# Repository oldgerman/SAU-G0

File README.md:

## SAU-G0

> 某存在感很弱的屑温湿度计（），美其名曰 Sensor Acquisition Unit（传感器采集单元）

- [1. 简介](#1-简介)
- [2. 续航](#2-续航)
  - [最低电流](#最低电流)
  - [最高电流](#最高电流)
  - [理论续航时间](#理论续航时间)
- [3. PCB](#3-pcb)
  - [SAU-G0（主控板）](#sau-g0主控板)
  - [SAU-G0-EX_AHT-GL（拓展版-AHT温湿度计-普通级）](#sau-g0-ex_aht-gl拓展版-aht温湿度计-普通级)
  - [SAU-G0-EX_AHT-PL（拓展版-AHT温湿度计-精准级）](#sau-g0-ex_aht-pl拓展版-aht温湿度计-精准级)
  - [SAU-G0-EX_microSD（拓展版-microSD）](#sau-g0-ex_microsd拓展版-microsd)
- [4. 焊接](#4-焊接)
- [5. BOM](#5-bom)
- [6. 软件](#6-软件)
  - [搭建环境](#搭建环境)
  - [功能进度](#功能进度)
  - [BUG fix progress](#bug-fix-progress)
- [7. 烧录](#7-烧录)
  - [ST-LINK](#st-link)
  - [ISP](#isp)
- [8. 成品](#8-成品)
- [9. 数据采集测试](#9-数据采集测试)
- [10. Acknowledgments](#10-acknowledgments)

## 1. 简介

SAU-G0（Sensor Acquisition Uinit（传感器采集单元），基于STM32G031G8U6，是本id学习低功耗的试水作品

## 2. 续航

### 最低电流

休眠：约8uA

亮屏运行：约4.0mA（1%屏幕亮度，WS2812不供电）

### 最高电流

最大电流30mA以上（OLED屏幕亮度100%，WS2812两通道LED亮度100%）

### 理论续航时间

使用CubeMX tools工具粗略计算（未引入唤醒瞬间的电流）：1%的时间运行，99%的时间休眠，每天运行864秒（屏幕亮度为1%），其他时间休眠，那么100mA锂电池极限续航2个月7天

如果每10分钟采集温湿度数据一次，每天采集144次，每次5秒，每天耗时720秒，还剩余144秒可支持每天以1%的亮度亮屏2分钟

每组带两位小数的温湿度数据占用4byte（16bit + 16bit），每天储存576byte数据，2个月采集温湿度数据8640组，占用34560byte空间（需使用24C512 EEPROM（65536byte）存储）

.png)

## 3. PCB

> PCB采用叠板设计，分为主控板与拓展板，具体应用取决于拓展板上的传感器和存储芯片，你可以绘制自己的拓展板写驱动程序

### SAU-G0（主控板）

- 硬件：STM32G031G8U6 + CH343P + LIS3DH + TPS63000 / TPS63001 + TP4054 / MCP73831-2ATI/OT

|  |  |  |
| -------------------------------------------------- | -------------------------------------------------------- | --------------------------------- |

- USB：由于只有一个Type-C，且休眠时（STOP1模式）固件没有禁用SWD接口功能（为了防止变砖，虽然STOP1模式用不了SWD），实测如果SWD接口用排阻连CH343的D+和D-会消耗200uA以上的电流，所以Type-C采用正反插不同功能，正插G031的SWD接口用于调试，反插USB转TTL串口，这样既保留功能也避免了电流泄露
- 串口芯片：可选焊接板载的CH343P，若想外接串口芯片节约成本，可焊接上图CH343P右边的两个焊接跳线，那么G031的USART2就与Type-C直连了
- 有源晶振：默认不焊接，使用内部振荡器，预留给更高精度的时钟应用，例如不使用拓展板的外置RTC，而使用G031内部的RTC，时钟源使用外部32.768Khz有源晶振

### SAU-G0-EX_AHT-GL（拓展板-AHT温湿度计-普通级）

- 硬件：AHT20 + 24Cxx + PCF8563 + WS2812

|  |  |  |
| ------------------------------------------------------------ | ------------------------------------------------------------ | ------------------------------------------------------------ |

### SAU-G0-EX_AHT-PL（拓展板-AHT温湿度计-精准级）

- 硬件：AHT20 + 24Cxx + PCF2129 + WS2812

|  |  |  |
| ------------------------------------------------------------ | ------------------------------------------------------------ | ------------------------------------------------------------ |

### SAU-G0-EX_microSD（拓展板-microSD）

- 硬件：microSD卡或NOR Flash + 12mm蜂鸣片
- 备注：无传感器和RTC芯片，整活儿专用，目前暂未写固件

|  |  |  |
| ------------------------------------------------------------ | ------------------------------------------------------------ | ------------------------------------------------------------ |

## 4. 焊接

SAU-G0主控单元有80多个元件，元件很密集（0402、扁平无引脚封装），十分建议开钢网

## 5. BOM

交互BOM，浏览器打开即可

路径：每一个AD工程目录下的 BOM/bom

电容耐压：OLED外围电路的几个电容标注了耐压要求，其他的电容默认10V耐压或以上

电池型号：601417 3.7V 100mAh

电池连接器：非必须，可以直接焊线

EEPROM：程序实现了容量 2Kbit-1024Kbit 自适应，推荐24C512

**OLED屏幕和FPC按键需要从豆总1.6元电子烟主板车上拆**（没有这个，但想DIY的朋友可以私信我给你寄）

## 6. 软件

### 搭建环境

打包的STM32CubeIDE1.7.0工程，需要先安装暗黑主题（[教程](https://blog.csdn.net/qq_42038029/article/details/99735688?utm_medium=distribute.pc_relevant.none-task-blog-title-2&spm=1001.2101.3001.4242)），然后随便编译/折腾

### 功能进度

目前固件已完成对AHT-GL和AHT-PL拓展板适配

- [x] 屏幕渐亮渐暗
- [x] 串口修改时间
- [x] 串口导出EEPROM储存的采集数据
- [x] 多级菜单
- [x] 自定义采集温湿度任务，自动计算任务数据存储空间
- [x] 自动检测EEPROM容量：已测试24C02、24C64、24C128、24C512
- [x] 休眠：支持RTC、加速度计、按键三种方式唤醒
- [ ] 串口命令解释器
- [ ] 硬件看门狗
- [ ] 熄屏采集逻辑

### BUG fix progress

- [ ] 硬复位时，检测EEPROM概率出现检测容量为0
- [ ] 唤醒时概率死机

## 7. 烧录

编译好的固件：[Hex](https://github.com/oldgerman/SAU-G0/tree/master/SoftWare/Hex)

Type-C采用正反插不同功能，正插G031的SWD接口用于调试，反插USB转TTL串口

烧录时需要全程按住按钮中键不放以保持上电

### ST-LINK

Type-C 正插连接即可烧录

### ISP

板载一键下载电路，Type-C 反插连接

STM32G031G8U6出厂时option bytes默认BOOT0信号由option byte决定，**ISP烧录前，必须先使用STLINK以SWD连G031修改option bytes的nBOOT_SEL位为取消勾选，否则后续CH343P的RTS和DTR无法将G031设置为IPS模式！！！**

需要FlyMCU和开STM32CubeProgrammer 配合烧录

**按住OK键保持不放**，FlyMCU选择 **RTS低电平DTR高电平进BooTloader**，显示已连接后（FlyMCU无法对G0进行进一步操作），**即可松开OK键**，然后打开STM32CubeProgrammer（FlyMCU可不关闭，另外新版STM32CubeProgrammer ，会有RTS和DTR选项，都选择0）以 UART **波特率115200** 连接，如果一切顺利，即可进入烧录状态

你可能会问为啥不直接用STM32CubeProgrammer操作DTR和RTS而要用FlyMCU操作，因为这个功能我测试对于一键下载电路不起作用，DTR和RTS信号的波形很奇怪，但是FlyMCU可以

## 8. 成品

### 外壳

- STL模型路径：[SAU-G0/Hardware/SW_Project/STL_OUT](https://github.com/oldgerman/SAU-G0/tree/master/Hardware/SW_Project/STL_OUT)

不同的打印方式需要使用不同的打印模型：

- FDM打印：上盖和盒子得分两个件打印，模型文件使用 **单个零件**
- 树脂光固化、尼龙激光烧结打印：盖子和盒子可合并成一个模型打印，模型文件使用 **连接零件**
- STL文件名解释：**GL**是使用PCF8563扩展板的，**PL**是使用PCF2129扩展板的

PA12打印的外壳组装后效果：

| .JPG) | .JPG) |
| ------------------------------------------------------ | :----------------------------------------------------- |
| .JPG) | .JPG) |

### 裸板

SAU-G0-EX_AHT-GL 初号机，AHT20 周边忘记开槽了：

|  |  |
| ------------------------------------------ | ------------------------------------- |

后续制作的 SAU-G0-EX_AHT-GL 和 SAU-G0-EX_AHT-PL：

|  |  |
| ------------------------------------------------------------ | ------------------------------------------------------------ |

## 9. BUG

### 死机

运行时，或唤醒时，都可能死机（概率极小），死机时，找一根USB线一端接5V，另一端 Type-C 反插连接温湿度计，然后拔出Type-C，即可复位STM32G031

### 串口导出的文本表格的格式不对

（待修复）串口导出的文本表格的格式不对，markdown表格记成csv格式，是说咋导入谷歌表格识别不了

### 扩展版

扩展板的纽扣电池保持开机亮屏才能从3V3充电，休眠或关机时无法充电，若太长时间不持续亮屏充电，由于RTC芯片持续消耗纽扣电池的能量，纽扣电池会过放电到0V

临时解决方案，例如 SAU-G0-EX_AHT-PL 扩展板，断开 SJ1跳线，将D1右端飞线到SJ2跳线的VbatWeek，这样后，即使关机了，锂电池还能经VbatWeek持续给纽扣电池充电

VbatWeek是从主板的锂电池经BAV99两个硅二极管降压取电的，压降1.1V左右。那么当主板的锂电池充满电时，即锂电池电压4.2V时，VbatWeek约3.1V，纽扣电池约3V，此时VbatWeek高于纽扣电池的电压时，RTC由VbatWeek供电（主板锂电池供电），而当锂电池低于4.1V时，纽扣电池的电压就会比VbatWeek高，RTC由纽扣电池供电，若熄屏时间太久没有唤醒，那么纽扣电池的电量会被RTC芯片持续消耗，可能出现纽扣电池的电压再次低于VbatWeek，那么纽扣电池又会充电

纽扣电池100%电量时电压约3V，0%电量时电压约2.0V，当纽扣电池低于2V时，主板锂电池也差不多低于3V触发锂电池保护板的过放电保护了，这个时候用户也会发现差不多没电了，需要充电

总之，纽扣电池和VbatWeek是通过二极管进行相互交替给RTC芯片供电的，在大多数情况下，当主板锂电池没电时，纽扣电池还能维持RTC芯片正常运转（MS621FE纽扣电池约5.5mAh，能维持RTC芯片（PCF2129：0.7uA）300天）

| 锂电池4.21V时，3.3V给纽扣电池充电，充满时纽扣电池的电压      | 锂电池4.20V时，VbatWeek的电压                         |
| ------------------------------------------------------------ | ----------------------------------------------------- |
|  |  |

后续有空就改一下PCB扩展版修这个电路BUG，如果我没有改，你也可以自己修改源文件

## 10. 数据采集测试

使用XCOM，连接串口黑屏就勾选RTS，再长按中键连接

菜单-->数据采集-->导出数据，文本表格格式为 csv 格式，数据以逗号分割，在XCOM里导出选中，复制，新建一个 .csv文件，粘贴进去，就可以用 Excel 或者 Google Sheets （谷歌表格） 处理

> 格式如下：
>
> ```c
> Date & Time        , T(C) , H(%)
> 2024/09/30 17:22:00, 31.90 ,51.00
> 2024/09/30 17:22:10, 31.90 ,49.00
> 2024/09/30 17:22:20, 31.80 ,40.00
> 2024/09/30 17:22:30, 31.70 ,44.00
> 2024/09/30 17:22:40, 31.70 ,44.00
> ```

例如，使用[谷歌表格](https://docs.google.com/spreadsheets/create?hl=zh-cn)，上传 csv 文件后，对列进行少许的格式化，得到折线图

采集数据的示例Excel文件位于[Data](https://github.com/oldgerman/SAU-G0/tree/master/Data)文件夹

[谷歌表格绘制折线图技巧](https://github.com/oldgerman/SAU-G0/tree/master/Data/谷歌表格绘制折线图技巧.md)

### 测试1：24小时1200+次采集

屏幕亮度90%，开启自动休眠，设置任务后，由RTC闹钟唤醒亮屏4秒，采集一次温湿度，数据保存在EEPROM，然后熄屏进入低功耗模式

在24小时如此反复约1200次，锂电池电压从4.2V降到4.0V，耗电约15%

左侧为温度标尺，右侧为湿度标尺，横轴为时间点（横轴无法显示完全1200个时间标签）

### 测试2：38天1800+次采集

屏幕亮度50%，开启自动休眠，设置任务后，由RTC闹钟唤醒亮屏5秒，采集一次温湿度，数据保存在EEPROM，然后熄屏进入低功耗模式

在38天如此反复约1800次（每天48次），锂电池电压从4.25V降到4.00V，耗电约20%

## 11.待开发

1. 加入默认任务模板：年采集，月采集，周采集
2. 这货要是flash再大点，可以整个串口命令进行报表查询

## 12. Acknowledgments

- 感谢[豆老板](https://oshwhub.com/red_bean)谈下1.6元电子烟主板车车
- 感谢 [JLC](https://www.jlc.com/) 制造的高品质 PCB
- 感谢稚晖 [Planck-Pi](https://github.com/peng-zhihui/Planck-Pi) 的 Type-C 正反插两用的灵感

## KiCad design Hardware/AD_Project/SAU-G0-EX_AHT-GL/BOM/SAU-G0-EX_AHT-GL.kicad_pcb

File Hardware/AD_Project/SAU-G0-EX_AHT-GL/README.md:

## SAU-G0-EX_AHT-GL

本目录为 SAU-G0-EX_AHT-GL 工程文件

工艺：

板厚1.0mm，双面板，过孔0.3/0.5mm，最小线宽线隙5mil

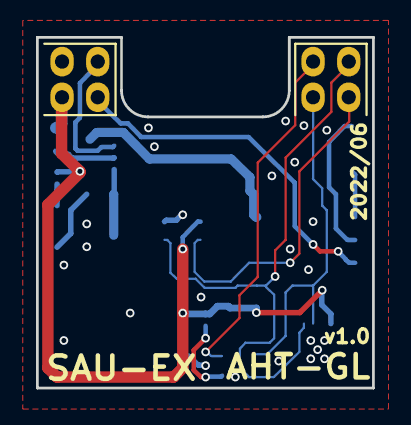
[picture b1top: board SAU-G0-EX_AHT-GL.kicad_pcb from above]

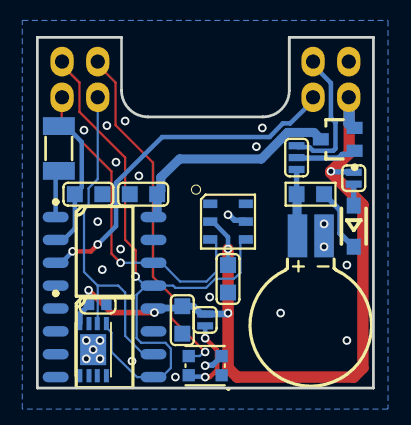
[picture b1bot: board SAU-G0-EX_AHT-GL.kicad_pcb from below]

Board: 2 copper layers, 18.7 x 19.5 mm, 22 parts (19 on the bottom side), 16 nets.

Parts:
BAT1: BAT; MS621FE-FL11E_1
C1: 6pF; C0603_1
C2, C3, C5: 100nF; C0603_1
C4: DNP; C0402_1
D1: B5819WS; SOD-323_1
ODG1, ODG2: ODG_LOGO; ODG_LOGO_soldermask_1
P1: Male; 2.0MM_MALE_2X2_2
P2: Male; 2.0mm_Male_2x2_1
R1: 620R; R0603_1
SJ1: SJ_3P; SJ_3P_MINI_1
SJ2, SJ3: SJ_2P; SJ_2P_MINI_1
U1: WS2812; WS2812_2020_1
U2: PCF8563; ANALOG_DEV_SOIC-8_R8_1
U3: 24Cxx_8P; ANALOG_DEV_SOIC-8_R8_1
U4: DNP_24Cxx_8P_DFN8_1EP; DFN-8-1EP_3x2mm_P0.5mm_EP1.70C
U5: AHT20; AHT20_1
VD1: BAT54C; DIODES_SOT-323-3_1
X1: 32.768KHz; XTAL_2P_3215_1

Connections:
3V3: C3.1, C4.1, C5.1, P2.3, SJ2.1, SJ3.2, U3.8, U4.8, U5.2, VD1.2
GND: BAT1.2, C1.1, C2.2, C3.2, C4.2, C5.2, P2.1, U1.2, U2.4, U3.1, U3.2, U3.3, U3.4, U3.7, U4.1, U4.2, U4.3, U4.4, U4.7, U4.9, U5.5
GPIO_ndef: P2.4, U2.3
NetC1_2: C1.2, U2.2, X1.1
NetC2_1: C2.1, U2.8, VD1.3
NetD1_1: D1.1, SJ3.1
NetD1_2: D1.2, R1.1
NetSJ1_2: SJ1.2, VD1.1
NetSJ2_2: SJ2.2, U1.4
NetU2_1: U2.1, X1.2
PB6_MISO2: P1.3, U3.6, U4.6
SCL1_SCK2: P1.4, U2.6, U5.3
SDA1_MOSI2: P1.2, U2.5, U3.5, U4.5, U5.4
SPI2_NSS: P1.1, U1.3
VbatWeek: P2.2, SJ1.1
Vbat_button: BAT1.1, R1.2, SJ1.3

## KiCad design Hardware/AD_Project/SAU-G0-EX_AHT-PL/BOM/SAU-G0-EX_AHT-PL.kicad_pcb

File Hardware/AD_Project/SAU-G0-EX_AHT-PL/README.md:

## SAU-G0-EX_AHT-PL

本目录为 SAU-G0-EX_AHT-PL 工程文件

工艺：

板厚1.0mm，双面板，过孔0.3/0.5mm，最小线宽线隙5mil

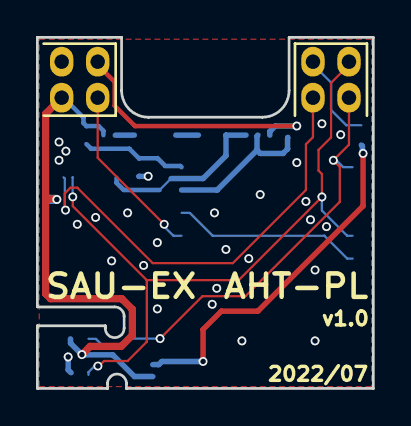
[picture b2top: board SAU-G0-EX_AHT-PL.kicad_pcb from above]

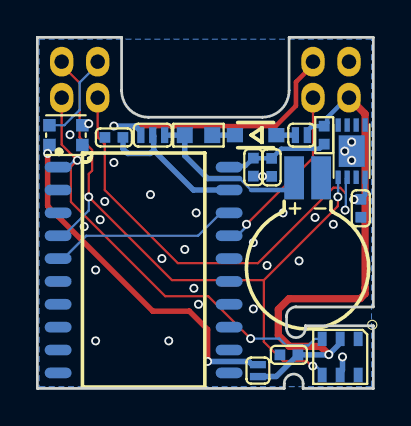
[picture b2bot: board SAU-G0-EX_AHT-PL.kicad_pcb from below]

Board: 2 copper layers, 18.7 x 19.5 mm, 20 parts (17 on the bottom side), 15 nets.

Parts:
BAT1: BAT; MS621FE-FL11E_1
C1, C3, C4, C5: 100nF; C0402_1
C2: 6.8uF; C0402_1
D1: B5819WS; SOD-323_1
ODG1, ODG2: ODG_LOGO; ODG_LOGO_soldermask_1
P1: Male; 2.0MM_MALE_2X2_2
P2: Male; 2.0mm_Male_2x2_1
R1: 330R; R0402_1
R2: 620R; R0603_1
SJ1, SJ3: SJ_2P; SJ_2P_MINI_1
SJ2: SJ_3P; SJ_3P_MINI_1
U1: AHT20; AHT20_1
U2: PCF2129; NXP_SO20_1
U3: DNP_24Cxx_8P_DFN8_1EP; DFN-8-1EP_3x2mm_P0.5mm_EP1.70C
U4: WS2812; WS2812_2020_1

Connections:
3V3: C1.1, C5.1, P2.3, R1.2, SJ1.2, SJ3.1, U1.2, U3.8
GND: BAT1.2, C1.2, C2.2, C3.2, C4.2, C5.2, P2.1, U1.5, U2.8, U3.1, U3.2, U3.3, U3.4, U3.7, U3.9, U4.2
GPIO_ndef: P2.4, U2.17
NetC2_1: C2.1, C3.1, R1.1, U2.20
NetC4_1: C4.1, SJ2.2, U2.19
NetD1_1: D1.1, SJ1.1
NetD1_2: D1.2, R2.1
NetSJ3_2: SJ3.2, U4.4
NetU2_5: U2.5, U2.18
PB6_MISO2: P1.3, U3.6
SCL1_SCK2: P1.4, U1.3, U2.1
SDA1_MOSI2: P1.2, U1.4, U2.4, U3.5
SPI2_NSS: P1.1, U4.3
VbatWeek: P2.2, SJ2.1
Vbat_button: BAT1.1, R2.2, SJ2.3

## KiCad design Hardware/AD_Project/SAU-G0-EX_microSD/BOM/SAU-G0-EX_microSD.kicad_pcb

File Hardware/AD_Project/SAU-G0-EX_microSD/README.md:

## SAU-G0-EX_microSD

本目录为 SAU-G0-EX_microSD 工程文件

工艺：

板厚1.0mm，双面板，过孔0.3/0.5mm，最小线宽线隙5mil

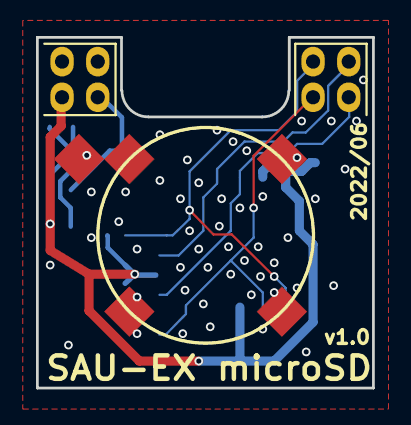
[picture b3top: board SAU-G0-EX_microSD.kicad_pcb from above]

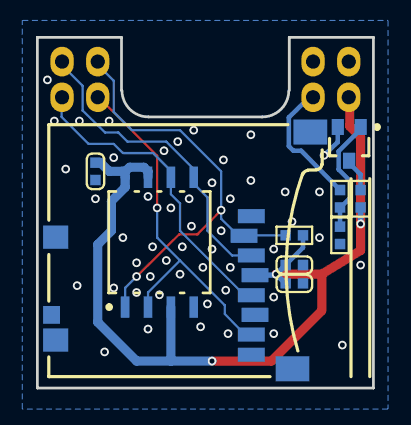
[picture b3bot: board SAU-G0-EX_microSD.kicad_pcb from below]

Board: 2 copper layers, 18.7 x 19.5 mm, 15 parts (11 on the bottom side), 10 nets.

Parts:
C1: 1uF; C0402_1
C2, C3: 100nF; C0402_1
LS1: 蜂鸣片12mm; С№µзМХґЙ·дГщЖ¬12MM_1
ODG1, ODG2: ODG_LOGO; ODG_LOGO_soldermask_1
P1: Male; 2.0MM_MALE_2X2_2
P2: Male; 2.0mm_Male_2x2_1
Q1: NPN; DIODES_SOT-323-3_1
R1: 100R; R0402_1
R2: 1K; R0402_1
R3: 10K; R0402_1
R4: 100K; R0402_1
SD1: Molex_473521001_microSD_Card; MOLEX_473521001_MICROSD_CARD_1
U1: W25Qxx; WIN_SS-8_WIN-L_1

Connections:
3V3: C1.2, C2.2, C3.1, P2.3, R1.2, R4.2, SD1.4, U1.3, U1.7, U1.8
GND: C1.1, C2.1, C3.2, LS1.2, LS1.2_1, LS1.2_2, LS1.2_3, P2.1, R3.1, SD1.6, SD1.9, SD1.10, SD1.10_1, SD1.10_2, SD1.10_3, U1.4
GPIO_ndef: P2.4, R2.1
NetLS1_1: LS1.1, Q1.2
NetQ1_1: Q1.1, R2.2, R3.2
NetQ1_3: Q1.3, R1.1
PB6_MISO2: P1.3, SD1.7, U1.2
SCL1_SCK2: P1.4, SD1.5, U1.6
SDA1_MOSI2: P1.2, SD1.3, U1.5
SPI2_NSS: P1.1, R4.1, SD1.2, U1.1

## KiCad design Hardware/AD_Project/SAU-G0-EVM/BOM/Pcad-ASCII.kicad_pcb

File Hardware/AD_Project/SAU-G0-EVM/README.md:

## SAU-G0-EVM

本PCB为评估版，G031的引脚、每个芯片电源引脚，都做了跳线设计，可以完全断开，以排查漏电流部分

没有本PCB，要想在SAU-G0主控板约2x2cm的极限尺寸上进行漏电流排查/抓波会非常麻烦

SAU-G0的绝大多数测试都在本PCB上完成验证，可做学习板之用

|  |  |
| ------------------------------------------------------------ | ------------------------------------------------------------ |

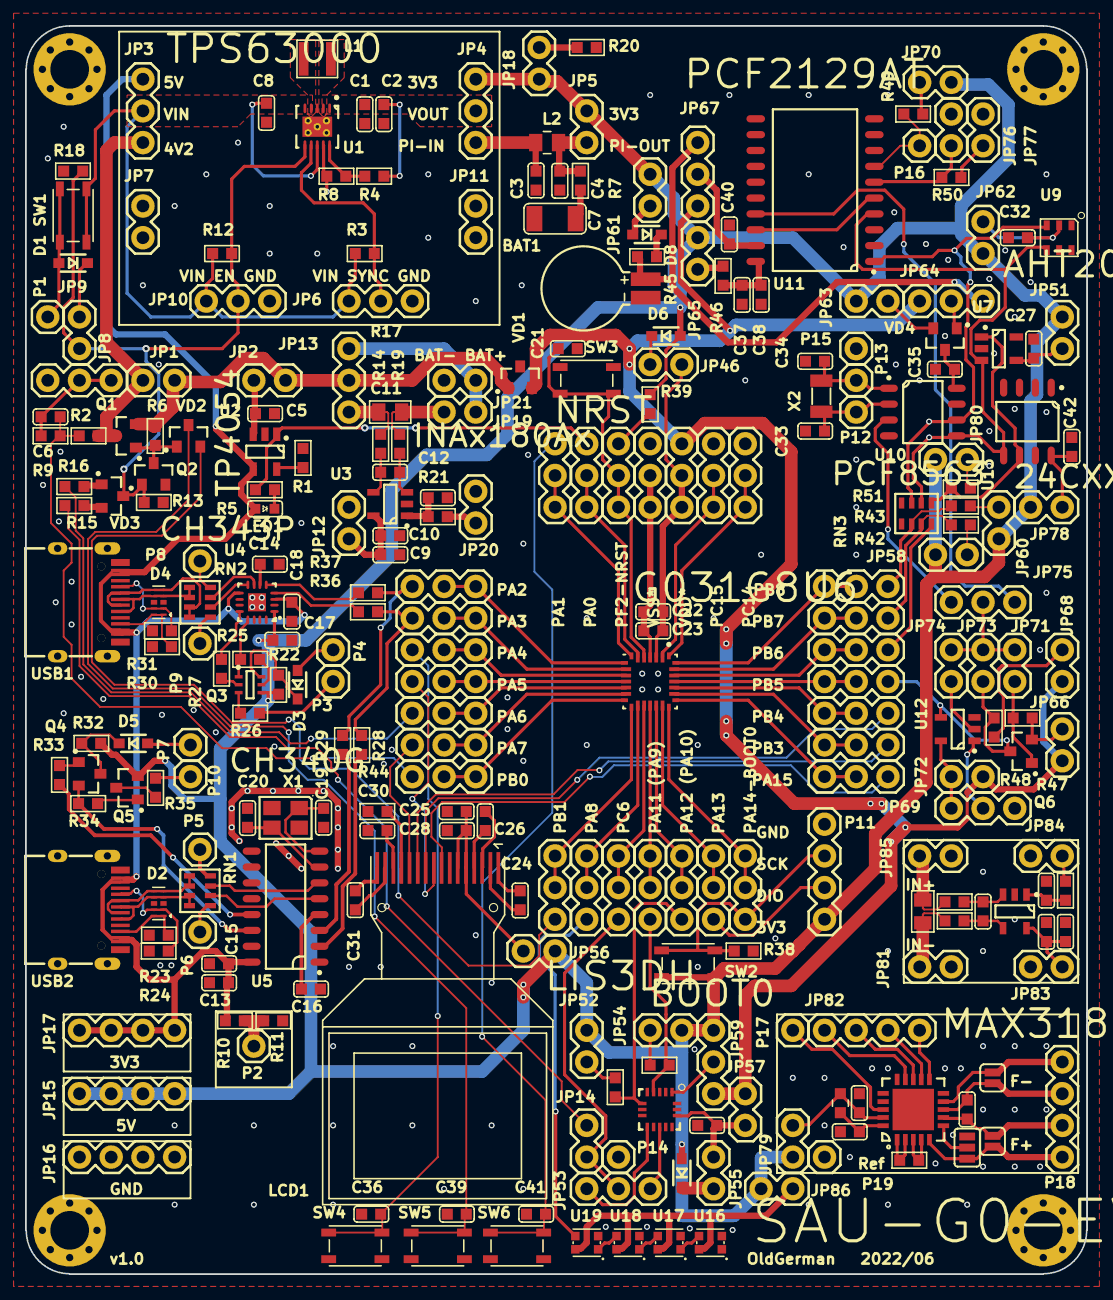
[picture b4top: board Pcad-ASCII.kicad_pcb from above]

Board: 2 copper layers, 85.0 x 100.0 mm, 275 parts (1 on the bottom side), 203 nets.

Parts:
BAT1: BAT; MS621FE-FL11E_1
C1, C2, C4, C8, C29: 10uF; C0603_1
C3: 10nF; C0603_1
C5, C9, C13, C24, C26, C45: 1uF; C0603_1
C6: 0.1uF; C0603_1
C7: 47uF; C1206_1
C10, C11, C12, C14, C15, C16, C17, C18, C21, C23, C27, C28, C32, C35, C36, C38, C39, C40, C41, C42, C43, C44, C46, C47, C48, C49: 100nF; C0603_1
C19, C20: 22pF; C0603_1
C22, C25, C30: 4.7uF; C0603_1
C31: 2.2uF; C0603_1
C33: 6pF; C0603_1
C34: NP; C0603_1
C37: 6.8uF; C0603_1
D1, D8: B5819WS; SOD-323_1
D2, D4: PESD1LVDS; DFN2510-10_SOT1165-1_1
D3: 1N4148WS; SOD-323_4
D5: DIODE; SOD-323_3
D6: B5819WS; SOD-323_5
D7: B5819WS; SOD-323_2
JP1, JP46, JP56, JP58, JP61, JP70, JP80, JP81, JP84: CONN_X2_DOT; 2.54mm_Male_x2_5
JP2, JP19, JP54, JP72, JP78, JP83, JP85, JP86: CONN_X2_DOT; 2.54mm_Male_x2_4
JP3, JP27, JP28, JP29, JP30, JP32, JP49, JP69, JP75: CONN_X3_DOT; 2.54mm_Male_x3_2
JP4: CONN_X3_DOT; 2.54mm_Male_x3_9
JP5: CONN_X2_DOT; 2.54mm_Male_x2_8
JP6, JP10, JP53, JP64: CONN_X3_DOT; 2.54mm_Male_x3_6
JP7: CONN_X2_DOT; 2.54mm_Male_x2_9
JP8: CONN_X3_DOT; 2.54mm_Male_x3_1
JP9, JP12, JP51, JP57, JP60, JP65, JP68, JP73, JP74: CONN_X2_DOT; 2.54mm_Male_x2_1
JP11: CONN_X2_DOT; 2.54mm_Male_x2_10
JP13, JP24, JP25: CONN_X3_DOT; 2.54mm_Male_x3_3
JP14: CONN_X2_DOT; 2.54mm_Male_x2_2
JP15, JP16, JP17: CONN_X4_DOT; 2.54mm_Male_x4_1
JP18, JP20, JP52, JP55, JP62, JP63, JP66, JP71, JP76, JP77: CONN_X2_DOT; 2.54mm_Male_x2_3
JP21: CONN_X2_DOT; 2.54mm_Male_x2_7
JP22, JP23: CONN_X3_DOT; 2.54mm_Male_x3_8
JP26, JP34, JP35, JP36, JP37, JP38, JP39, JP40, JP44, JP59: CONN_X3_DOT; 2.54mm_Male_x3_4
JP31, JP33, JP41, JP42, JP43, JP45, JP47, JP48, JP50: CONN_X3_DOT; 2.54mm_Male_x3_7
JP67: CONN_X3_DOT; 2.54mm_Male_x3_5
JP79: CONN_X2_DOT; 2.54mm_Male_x2_6
JP82: CONN_X4_DOT; 2.54mm_Male_x4_2
L1: Inductor_power; IND-30301X_1
L2: 10uH; FER0805_1
L3: 10uH; FER0603_1
LCD1: OLED_SPI_16PIN; oled_64x48_0.66_SSD1306_TOP_6E
LED1: LED; LED0603_WHITE_1
ODG1, ODG2: ODG_LOGO; ODG_LOGO_soldermask_1
P1, P2, P5, P6, P8, P9, P12, P13, P14, P15, P16, P17, P19: CONN_X1_DOT; 2.54mm_Male_x1_1
P3, P4, P7: CONN_X1_DOT; 2.54mm_Male_x1_3
P10: CONN_X1_DOT; 2.54mm_Male_x1_2
P11: CONN_X4; 2.54mm_Male_x4_4
P18: CONN_X4; 2.54mm_Male_x4_3
Q1, Q6: P-MOS; INFINEON_SOT-23-3_1
Q2: N-MOS; INFINEON_SOT-23-3_1
Q3: LMBT3946DW1T1G; ON_SEMI_SOT-363_1
Q4: S8050; INFINEON_SOT-23-3_1
Q5: S8550; INFINEON_SOT-23-3_1
R1: 20K; R0603_1
R2, R6, R9, R13, R47: 100K; R0603_1
R3, R4, R12: 1M; R0603_1
R5, R21, R25, R26, R27, R33, R34, R35: 1K; R0603_1
R7: 0.33R; R0603_1
R8: 178K; R0603_1
R10, R11, R15, R16, R22, R32, R38, R39, R48, R49: 10K; R0603_1
R14, R19, R53, R55: 10R; R0603_1
R17, R54: 2R 0.1%; R0805_1
R18: DNP; R0603_1
R20: 47K; R0603_1
R23, R24, R30, R31, R40, R41: 5.1K; R0603_1
R28, R29, R36, R37: 0R; R0603_1
R42, R43, R51: 3K; R0603_1
R44: 390K; R0603_1
R45: 620R; R0603_1
R46, R56: 330R; R0603_1
R50: 220K; R0603_1
R52: 430R 0.1%; R0603_1
RN1, RN2: 22R; RESNET_1206-8_CONCAVE_1
RN3: 100R; RESNET_1206-8_CONCAVE_1
SJ1: SJ_3P; SJ_3P_1
SJ2, SJ3: SJ_2P; SJ_2P_1
SUN_HOLE1, SUN_HOLE2, SUN_HOLE3, SUN_HOLE4: SUN_HOLE; SUN_HOLE_M3_1
SW1, SW2, SW3, SW4, SW5, SW6: Button-4P; SWITCH_3X4X2.5_4PIN_SMD_1
U1: TPS63000; TI_PVSON-10_3x3MM_DRC_1
U2: MCP73831T; MICROCHIP_SOT-23-5_OT_1
U3, U15: INA180A3; TI_SOT-23-5_DBV_1
U4: CH343P; Analog_QFN-16_3x3MM_1
U5: CH340G; TI_SOP-16_D_1
U6: STM32G031G8U6; UFQFPN28-4x4mm_ODG_1
U7: 24Cxx_SOT23-5; MICROCHIP_SOT-23-5_OT_1
U8: LIS3DH; LGA-16-3X3_1
U9: AHT20; AHT20_1
U10: PCF8563; ANALOG_DEV_SOIC-8_R8_1
U11: PCF2129; NXP_SO20_1
U12: SN74LVC1G04DBVR; TI_SOT-23-5_DBV_1
U13: 24Cxx_8P; ANALOG_DEV_SOIC-8_R8_1
U14: MAX31865; VQFN-20_5x5MM_0.65_1
U16: WS2812; WS2812_2020_1
U17, U18, U19: WS2812; WS2812_2020_2
USB1, USB2: Type-C; Type-C-TOP_1
VD1: BAV99; INFINEON_SOT-23-3_1
VD2, VD3, VD4: BAT54C; INFINEON_SOT-23-3_1
X1: XTAL-4P; EPSON_TSX-3225_1
X2: XTAL-2P; XTAL_2P_3215_1

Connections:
3V3: C17.2, D6.1, D7.1, JP4.1, JP5.2, JP15.1, JP15.2, JP15.3, JP15.4, JP18.1, JP51.1, JP52.2, JP54.2, JP56.1, JP58.2, JP59.1, JP60.2, JP61.1, JP62.1, JP63.1, JP65.1, JP70.1, JP78.1, JP79.1, JP80.2, JP86.1, P11.4, Q3.4, Q5.2, R22.1, R32.1, R39.2, SW2.3, SW2.4, U4.1
4V2: JP1.2, JP3.1, Q1.3, R2.2
5V_Info: P2.1, R10.1, R11.2
+5: C13.2, C15.2, C18.2, JP3.3, JP17.1, JP17.2, JP17.3, JP17.4, LED1.1, R10.2, U2.4, U4.3, U4.9, U5.16, USB1.A4, USB1.A9, USB1.B4, USB1.B9, USB2.A4, USB2.A9, USB2.B4, USB2.B9
BAT+: JP13.3, JP19.2, JP21.1
BAT_INFO: C6.1, JP32.3, R2.1, R9.2
BOOT01: P3.1, R26.1
BOOT02: P10.1, R35.2
CC1-1: D4.2, D4.9, R31.2, USB1.A5
CC1-2: D2.2, D2.9, R24.2, USB2.A5
CC2-1: D4.1, D4.10, R30.1, USB1.B5
CC2-2: D2.1, D2.10, R23.1, USB2.B5
CH340_D+: RN1.2, U5.5
CH340_D-: RN1.3, U5.6
CH340_RX: R29.1, U5.3
CH340_TX: R28.1, U5.2
CH343_D+: RN2.3, U4.7
CH343_D-: RN2.2, U4.8
CH343_RX: R37.1, U4.5
CH343_TX: R36.1, U4.4
Charge_Detect: JP23.3, R5.1, U2.1
D1+: D4.4, D4.7, RN2.5, RN2.6, USB1.A6, USB1.B6
D1-: D4.5, D4.6, RN2.7, RN2.8, USB1.A7, USB1.B7
D2+: D2.4, D2.7, RN1.7, RN1.8, USB2.A6, USB2.B6
D2-: D2.5, D2.6, RN1.5, RN1.6, USB2.A7, USB2.B7
DISP_CS: JP41.3, LCD1.8
DISP_DC: JP43.3, LCD1.10
DISP_RES: JP28.3, LCD1.9
FB: R4.1, R8.1, U1.10
G0_VDD: C22.1, C23.1, JP44.2, JP44.3, JP46.1, U6.3
GND: BAT1.2, C1.2, C2.2, C3.1, C4.2, C5.2, C7.2, C8.2, C9.2, C10.2, C12.2, C13.1, C14.2, C15.1, C16.2, C17.1, C18.1, C19.1, C20.1, C21.2, C22.2, C23.2, C25.2, C27.2, C28.1, C29.2, C30.2, C31.2, C32.2, C33.1, C34.1, C35.2, C36.1, C37.2, C38.2, C39.1, C40.2, C41.1, C42.2, C43.2, C44.2, C45.2, C46.2, C49.2, D2.3, D2.8, D4.3, D4.8, JP6.3, JP7.1, JP7.2, JP8.3, JP10.3, JP11.1, JP11.2, JP12.1, JP16.1, JP16.2, JP16.3, JP16.4, JP20.2, JP21.2, JP49.1, JP49.2, JP49.3, JP69.1, JP76.2, JP77.2, JP81.1, JP83.1, JP84.2, JP85.2, LCD1.7, LCD1.16, P11.1, P14.1, P15.1, P19.1, Q2.2, R1.1, R8.2, R11.1, R13.1, R18.1, R20.1, R23.2, R24.1, R30.2, R31.1, R38.2, R44.1, SJ1.3, SW3.1, SW3.2, SW4.1, SW4.2, SW5.1, SW5.2, SW6.1, SW6.2, U1.3, U1.9, U1.11, U1.V:Ex24y24d121, U2.2, U3.2, U4.2, U4.17, U5.1, U6.4, U7.2, U7.5, U8.5, U8.10, U8.12, U9.5, U10.4, U11.8, U12.3, U13.1, U13.2, U13.3, U13.4, U13.7, U14.10, U14.15, U14.16, U14.21, U15.2, U16.2, U17.2, U18.2, U19.2, USB1.1, USB1.2, USB1.3, USB1.4, USB1.A1, USB1.A12, USB1.B1, USB1.B12, USB2.1, USB2.2, USB2.3, USB2.4, USB2.A1, USB2.A12, USB2.B1, USB2.B12, X1.2, X1.4
GPIO_ndef: JP45.3, JP73.2, Q6.3, R48.2, U12.4
I2C1_SCL_SPI2_SCK: JP50.3, R43.2, RN3.2
I2C1_SDA_SPI2_MOSI: JP48.3, R42.2, RN3.3
I2C2_SCL: JP37.3, R41.2, U8.4
I2C2_SDA: JP39.3, R40.2, U8.6
IN-_INA: JP1.1, JP2.2, JP13.2, Q1.2, R6.2, VD1.1
INT: JP14.1, JP36.3, JP53.2
INT1: JP53.3, U8.11
INT2: JP53.1, U8.9
INT_PCF2129: JP75.1, U11.17
INT_PCF8563: JP75.3, U10.3
KEY1: C41.2, JP25.3, SW6.3, SW6.4
KEY2: C39.2, SW5.3, SW5.4, VD2.3
KEY3: C36.2, JP27.3, SW4.3, SW4.4
KEY_OK: JP34.3, VD2.2
LIPO+: C5.1, JP2.1, U2.3
N_R_S_T_1: D3.1, P4.1
N_R_S_T_2: D5.1, P7.1
NetC3_2: C3.2, JP4.3, L2.1
NetC4_1: C4.1, JP5.1, L2.2, R7.2
NetC6_2: C6.2, JP8.1, JP8.2, R9.1
NetC7_1: C7.1, R7.1
NetC8_1: C8.1, JP3.2, JP6.1, JP10.1, R3.1, R12.1, SW1.3, SW1.4, U1.5, U1.8
NetC11_1: C11.1, R19.1, U3.3
NetC11_2: C11.2, R14.1, U3.4
NetC12_1: C12.1, R21.2, U3.1
NetC14_1: C14.1, U4.6
NetC16_1: C16.1, U5.4
NetC19_2: C19.2, U5.8, X1.1
NetC20_2: C20.2, U5.7, X1.3
NetC24_1: C24.1, LCD1.1
NetC24_2: C24.2, LCD1.2
NetC25_1: C25.1, C28.2, JP56.2, LCD1.5, LCD1.6
NetC26_1: C26.1, LCD1.3
NetC26_2: C26.2, LCD1.4
NetC27_1: C27.1, JP51.2, U7.4
NetC29_1: C29.1, JP55.2, JP57.2, U8.14
NetC30_1: C30.1, LCD1.14
NetC31_1: C31.1, LCD1.15
NetC32_1: C32.1, JP62.2, U9.2
NetC33_2: C33.2, P12.1, U10.2, X2.1
NetC34_2: C34.2, P13.1, U10.1, X2.2
NetC35_1: C35.1, U10.8, VD4.3
NetC37_1: C37.1, C38.1, R46.1, U11.20
NetC40_1: C40.1, JP67.2, U11.19
NetC42_1: C42.1, JP78.2, U13.8
NetC43_1: C43.1, JP79.2, L3.2, U14.19
NetC44_1: C44.1, L3.1, U14.20
NetC47_1: C47.1, P18.2, SJ2.2, U14.7
NetC47_2: C47.2, P18.3, SJ3.1, U14.8
NetC48_1: C48.1, R55.1, U15.3
NetC48_2: C48.2, R53.1, U15.4
NetC49_1: C49.1, R56.2, U15.1
NetD1_1: D1.1, P1.1, SW1.1, SW1.2
NetD1_2: D1.2, JP9.1
NetD3_2: D3.2, Q3.6, R22.2
NetD5_2: D5.2, Q4.3, R32.2
NetD6_2: D6.2, JP46.2
NetD7_2: D7.2, JP55.1
NetD8_1: D8.1, JP61.2
NetD8_2: D8.2, R45.1
NetJP6_2: JP6.2, R3.2, U1.7
NetJP9_2: JP9.2, JP10.2, Q2.1, R12.2, R13.2, R18.2, U1.6, VD3.3
NetJP13_1: JP13.1, R14.2, R17.1
NetJP14_2: JP14.2, R15.1
NetJP18_2: JP18.2, R20.2
NetJP19_1: JP19.1, R17.2, R19.2
NetJP26_1: JP26.1, R39.1
NetJP52_1: JP52.1, R40.1
NetJP54_1: JP54.1, R41.1
NetJP58_1: JP58.1, R42.1
NetJP59_2: JP59.2, U8.1
NetJP60_1: JP60.1, R43.1
NetJP63_2: JP63.2, VD4.2
NetJP64_2: JP64.2, VD4.1
NetJP65_2: JP65.2, R46.2
NetJP66_2: JP66.2, Q6.2, R47.2
NetJP68_1: JP68.1, R48.1
NetJP69_2: JP69.2, U12.1
NetJP69_3: JP69.3, JP72.1, U12.5
NetJP70_2: JP70.2, R49.2
NetJP71_1: JP71.1, JP73.1, JP74.1, JP75.2
NetJP71_2: JP71.2, Q6.1, R47.1
NetJP74_2: JP74.2, U12.2
NetJP76_1: JP76.1, R50.2, U11.6
NetJP77_1: JP77.1, R50.1
NetJP80_1: JP80.1, R51.2
NetJP81_2: JP81.2, R53.2, R54.1
NetJP82_1: JP82.1, U14.11
NetJP82_2: JP82.2, U14.12
NetJP82_3: JP82.3, U14.13
NetJP82_4: JP82.4, U14.14
NetJP85_1: JP85.1, R54.2, R55.2
NetJP86_2: JP86.2, U16.4, U17.4, U18.4, U19.4
NetL1_1: L1.1, U1.4
NetL1_2: L1.2, U1.2
NetLCD1_13: LCD1.13, R44.2
NetLED1_2: LED1.2, R5.2
NetP16_1: P16.1, R49.1, U11.7
NetP17_1: P17.1, U14.18
NetP18_1: P18.1, SJ1.1, SJ2.1, U14.5
NetP18_4: P18.4, SJ3.2, U14.9
NetQ1_1: Q1.1, Q2.3, R6.1, VD2.1
NetQ3_1: Q3.1, R25.2, U4.13
NetQ3_2: Q3.2, R27.2
NetQ3_3: Q3.3, R26.2
NetQ3_5: Q3.5, R25.1
NetQ4_1: Q4.1, R33.1
NetQ4_2: Q4.2, R34.2, U5.14
NetQ5_1: Q5.1, R34.1
NetQ5_3: Q5.3, R35.1
NetR1_2: R1.2, U2.5
NetR15_2: R15.2, VD3.2
NetR16_2: R16.2, VD3.1
NetR27_1: R27.1, U4.12
NetR33_2: R33.2, U5.13
NetR52_1: R52.1, U14.3, U14.4
NetR52_2: R52.2, U14.1, U14.2
NetSJ1_2: SJ1.2, U14.6
NetU11_5: U11.5, U11.18
NetU16_3: U16.3, U17.1
NetU17_3: U17.3, U18.1
NetU18_3: U18.3, U19.1
OUT_INA1: JP20.1, R21.1
OUT_INA2: JP84.1, R56.1
PA0: JP23.1, JP23.2, U6.6
PA1: JP25.1, JP25.2, U6.7
PA2: JP33.2, JP33.3, U6.8
PA2_TX: JP33.1, R29.2, R37.2
PA3: JP31.2, JP31.3, U6.9
PA3_RX: JP31.1, R28.2, R36.2
PA4: JP27.1, JP27.2, U6.10
PA5: JP28.1, JP28.2, U6.11
PA6: JP29.1, JP29.2, U6.12
PA7: JP30.1, JP30.2, U6.13
PA8: JP35.1, JP35.2, U6.16
PA11: JP37.1, JP37.2, U6.18
PA12: JP39.1, JP39.2, U6.19
PA13: JP22.2, JP22.3, U6.20
PA14: JP24.2, JP24.3, U6.21
PA15: JP41.1, JP41.2, U6.22
PB0: JP32.1, JP32.2, U6.14
PB1: JP34.1, JP34.2, U6.15
PB3: JP42.1, JP42.2, U6.23
PB4: JP43.1, JP43.2, U6.24
PB5: JP45.1, JP45.2, U6.25
PB6: JP47.1, JP47.2, U6.26
PB6_MISO2: R51.1, RN3.5, U7.1, U13.6
PB7: JP48.1, JP48.2, U6.27
PB8: JP50.1, JP50.2, U6.28
PC6: JP36.1, JP36.2, U6.17
PC14: JP38.2, JP38.3, U6.1
PC15: JP40.2, JP40.3, U6.2
PF2_N_R_S_T_: C21.1, JP26.2, JP26.3, SW3.3, SW3.4, U6.5
PW_HOLD: JP29.3, R16.1
SCL1_SCK2: RN3.7, U9.3, U10.6, U11.1
SDA1_MOSI2: RN3.6, U7.3, U9.4, U10.5, U11.4, U13.5
SPI1_MOSI: JP30.3, LCD1.12
SPI1_SCK: JP42.3, LCD1.11
SPI2_MISO: JP47.3, RN3.4
SPI2_NSS: JP35.3, U19.3
SWCLK1: P8.1, RN2.4
SWCLK2: P6.1, RN1.1
SWCLK_BOOT0: JP24.1, P11.2, R38.1, SW2.1, SW2.2
SWDIO: JP22.1, P11.3
SWDIO_BOOT01: P9.1, RN2.1
SWDIO_BOOT02: P5.1, RN1.4
TPS_VOUT: C1.1, C2.1, JP4.2, R4.2, U1.1
VDD_INA1: C9.1, C10.1, JP12.2, U3.5
VDD_INA2: C45.1, C46.1, JP83.2, U15.5
VbatWeek: JP44.1, JP57.1, JP59.3, JP64.1, JP66.1, JP67.1, JP68.2, JP72.2, VD1.2
Vbat_button: BAT1.1, JP64.3, JP67.3, R45.2

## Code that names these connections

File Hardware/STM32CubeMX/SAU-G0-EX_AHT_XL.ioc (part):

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Mcu.Name=STM32G031G(4-6-8)Ux
Mcu.Package=UFQFPN28
Mcu.UserName=STM32G031G8Ux
PA0.GPIOParameters=GPIO_Label
PA0.GPIO_Label=KEY2
PA0.Signal=GPIO_Input
PA1.GPIOParameters=GPIO_Label
PA1.GPIO_Label=KEY1
PA1.Signal=GPIO_Input
PA11\ [PA9].Mode=I2C
PA11\ [PA9].Signal=I2C2_SCL
PA12\ [PA10].Mode=I2C
PA12\ [PA10].Signal=I2C2_SDA
PA13.Mode=Serial_Wire
PA13.Signal=SYS_SWDIO
PA14-BOOT0.Mode=Serial_Wire
PA14-BOOT0.Signal=SYS_SWCLK
PA15.Mode=NSS_Signal_Hard_Output
PA15.Signal=SPI1_NSS
PA2.Signal=USART2_TX
PA3.Signal=USART2_RX
PA4.GPIOParameters=GPIO_Label
PA4.GPIO_Label=KEY3
PA4.Signal=GPIO_Input
PA5.GPIOParameters=GPIO_Label
PA5.GPIO_Label=DISP_RES
PA5.Signal=GPIO_Output
PA6.GPIOParameters=GPIO_Label
PA6.GPIO_Label=PW_HOLD
PA6.Signal=GPIO_Output
PA7.Mode=TX_Only_Simplex_Unidirect_Master
PA7.Signal=SPI1_MOSI
PA8.Signal=SPI2_NSS
PB0.GPIOParameters=GPIO_Label
PB0.GPIO_Label=BAT_INFO
PB0.Mode=IN8
PB0.Signal=ADC1_IN8
PB1.GPIOParameters=GPIO_Label
PB1.GPIO_Label=PKEY_STA
PB1.Signal=GPIO_Output
PB3.Mode=TX_Only_Simplex_Unidirect_Master
PB3.Signal=SPI1_SCK
PB4.GPIOParameters=GPIO_Label
PB4.GPIO_Label=DISP_DC
PB4.Signal=GPIO_Output
PB5.Mode=SYS_WakeUp6
PB5.Signal=SYS_WKUP6
PB6.Signal=SPI2_MISO
PB7.Signal=I2C1_SDA
PB8.Signal=I2C1_SCL
PC6.GPIOParameters=GPIO_Label
PC6.GPIO_Label=Charge_Detect
PC6.Signal=GPIO_Input
RCC.HSE_VALUE=8000000
RCC.SYSCLKFreq_VALUE=125000
board=custom

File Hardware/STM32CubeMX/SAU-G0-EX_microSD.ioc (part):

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Mcu.Name=STM32G031G(4-6-8)Ux
Mcu.Package=UFQFPN28
Mcu.UserName=STM32G031G8Ux
PA0.GPIOParameters=GPIO_Label,GPIO_ModeDefaultEXTI
PA0.GPIO_Label=INT_IMU
PA0.GPIO_ModeDefaultEXTI=GPIO_MODE_IT_FALLING
PA0.Signal=GPXTI0
PA1.GPIOParameters=GPIO_PuPd,GPIO_Label
PA1.GPIO_Label=KEY_A
PA1.GPIO_PuPd=GPIO_PULLUP
PA1.Signal=GPIO_Input
PA11\ [PA9].GPIOParameters=GPIO_Label
PA11\ [PA9].GPIO_Label=SCL2
PA11\ [PA9].Mode=I2C
PA11\ [PA9].Signal=I2C2_SCL
PA12\ [PA10].GPIOParameters=GPIO_Label
PA12\ [PA10].GPIO_Label=SDA2
PA12\ [PA10].Mode=I2C
PA12\ [PA10].Signal=I2C2_SDA
PA13.Mode=Serial_Wire
PA13.Signal=SYS_SWDIO
PA14-BOOT0.Mode=Serial_Wire
PA14-BOOT0.Signal=SYS_SWCLK
PA15.Mode=NSS_Signal_Hard_Output
PA15.Signal=SPI1_NSS
PA2.Mode=Asynchronous
PA2.Signal=USART2_TX
PA3.Mode=Asynchronous
PA3.Signal=USART2_RX
PA4.GPIOParameters=GPIO_PuPd,GPIO_Label
PA4.GPIO_Label=KEY_B
PA4.GPIO_PuPd=GPIO_PULLUP
PA4.Signal=GPIO_Input
PA5.GPIOParameters=GPIO_Label
PA5.GPIO_Label=DISP_RES
PA5.Signal=GPIO_Output
PA6.GPIOParameters=GPIO_Label
PA6.GPIO_Label=PW_HOLD
PA6.Signal=GPIO_Output
PA7.Mode=TX_Only_Simplex_Unidirect_Master
PA7.Signal=SPI1_MOSI
PA8.Mode=NSS_Signal_Hard_Output
PA8.Signal=SPI2_NSS
PB0.GPIOParameters=GPIO_Label
PB0.GPIO_Label=BAT_INFO
PB0.Mode=IN8
PB0.Signal=ADC1_IN8
PB1.GPIOParameters=GPIO_PuPd,GPIO_Label,GPIO_ModeDefaultEXTI
PB1.GPIO_Label=KEY_OK
PB1.GPIO_ModeDefaultEXTI=GPIO_MODE_IT_FALLING
PB1.GPIO_PuPd=GPIO_PULLUP
PB1.Signal=GPXTI1
PB3.Mode=TX_Only_Simplex_Unidirect_Master
PB3.Signal=SPI1_SCK
PB4.GPIOParameters=GPIO_Label
PB4.GPIO_Label=DISP_DC
PB4.Signal=GPIO_Output
PB5.Signal=S_TIM3_CH2
PB6.Mode=Full_Duplex_Master
PB6.Signal=SPI2_MISO
PB7.Mode=Full_Duplex_Master
PB7.Signal=SPI2_MOSI
PB8.Mode=Full_Duplex_Master
PB8.Signal=SPI2_SCK
PC14-OSC32_IN\ (PC14).Mode=HSE-External-Clock-Source
PC14-OSC32_IN\ (PC14).Signal=RCC_OSC_IN
PC15-OSC32_OUT\ (PC15).Signal=GPIO_Output
PC6.GPIOParameters=GPIO_PuPd,GPIO_Label
PC6.GPIO_Label=CHARGE_DETECT
PC6.GPIO_PuPd=GPIO_PULLUP
PC6.Signal=GPIO_Input
RCC.HSE_VALUE=8000000
RCC.SYSCLKFreq_VALUE=64000000
RCC.SYSCLKSource=RCC_SYSCLKSOURCE_PLLCLK
board=custom

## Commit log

2022-05-25 修改Buttons库的F和B映射到B和A
2022-05-27 适配Colum和Page的值修改显示
2022-05-27 readme图片修改
2022-05-27 readme添加统一改为uint16_t的说明
2022-05-31 RTClib修复读写API、EE24升级为类
2022-06-01 修复可以修改位域Colum类进入修改模式时可能卡死的BUG，实现任务设置下所有功能
2022-06-05 新增一些功能的实现
2022-06-06 修改了仓库名
2022-06-06 目录结构变更
2022-06-23 实现RTC从STOP1唤醒定时任务
2022-06-24 优化风扇卡顿
2022-06-24 打包BSP_TH.cpp
2022-06-24 打包USART和TH到BSP，修复串口无法修改时间的BUG
2022-06-24 修复使用ST_MEMS库时，触发阈值设定值没有更新到LIS3DH寄存器
2022-06-24 修复采集数据无法记录，原因是没有ee24.exchangeI2Cpins()
2022-06-24 修复BSP打包Contrast后，亮屏逐渐变亮失效
2022-06-24 添加RTC_AlarmWillTrigger_MiniumSecond的取值注释
2022-06-27 修复EE24单位换算BUG，添加自检EEPROM容量
2022-06-27 更正电池页ADC数据右对齐
2022-06-28 修复STOP1唤醒后充电时2812不亮的问题
2022-06-29 完成PCF8563适配，修复RTClib和扫描I2C设备的BUG
2022-07-06 添加脑图、AD工程文件、元件手册
2022-07-06 添加README目录
2022-07-06 移除ref目录
2022-07-07 添加拓展板拼板工程和README
2022-07-07 移除一些多余的文件
2022-07-09 修复SAU-G0-EX_Splicing外形层缺失AHT20锣槽
2022-07-14 修改I2C1为100KHz，添加硬件文件
2022-07-14 添加SAU-G0-EVM预览图
2022-07-14 修改readme
2023-06-18 2023-06-18_22:31 补充 UART 烧录固件描述不清楚的地方
2023-12-13 2023-12-13_15:54
2023-12-13 2023-12-13_15:55
2024-03-26 2024-0326_18:02
2024-04-08 2024-0407_22:54
2024-04-10 2024-0410_21:27
2024-04-11 2024-0411_21:19
2024-05-17 2024-0517_21:00
2024-08-27 2024-0827_11:54
2024-09-14 2024-0914_16:39
2024-09-30 2024-0930_17:37
